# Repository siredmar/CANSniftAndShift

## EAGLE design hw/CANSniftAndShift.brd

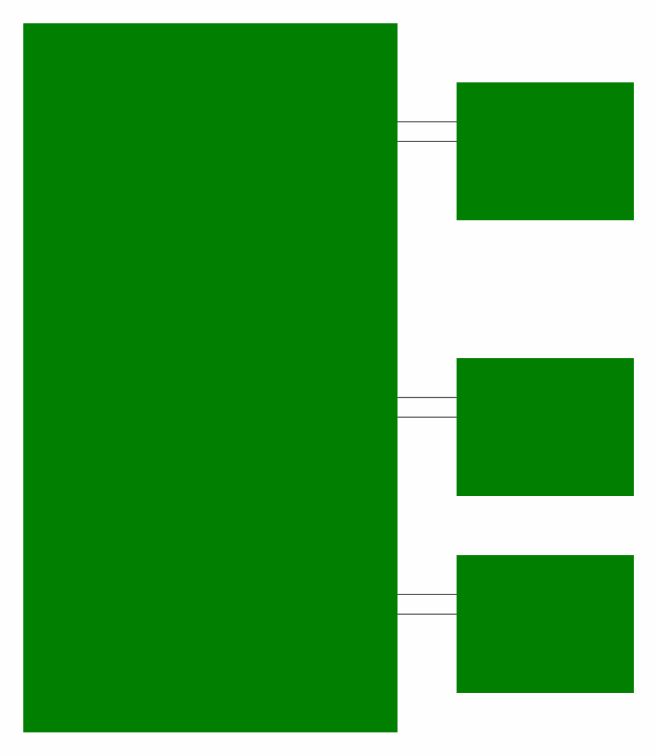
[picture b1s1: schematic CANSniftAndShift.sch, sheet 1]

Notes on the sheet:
CAN0
CAN1
CPU
FTDI
FTDI_RX
FTDI_TX
TXD
RXD
CAN0RX
CAN1RX
CAN0TX
CAN1TX
CANH
CANL

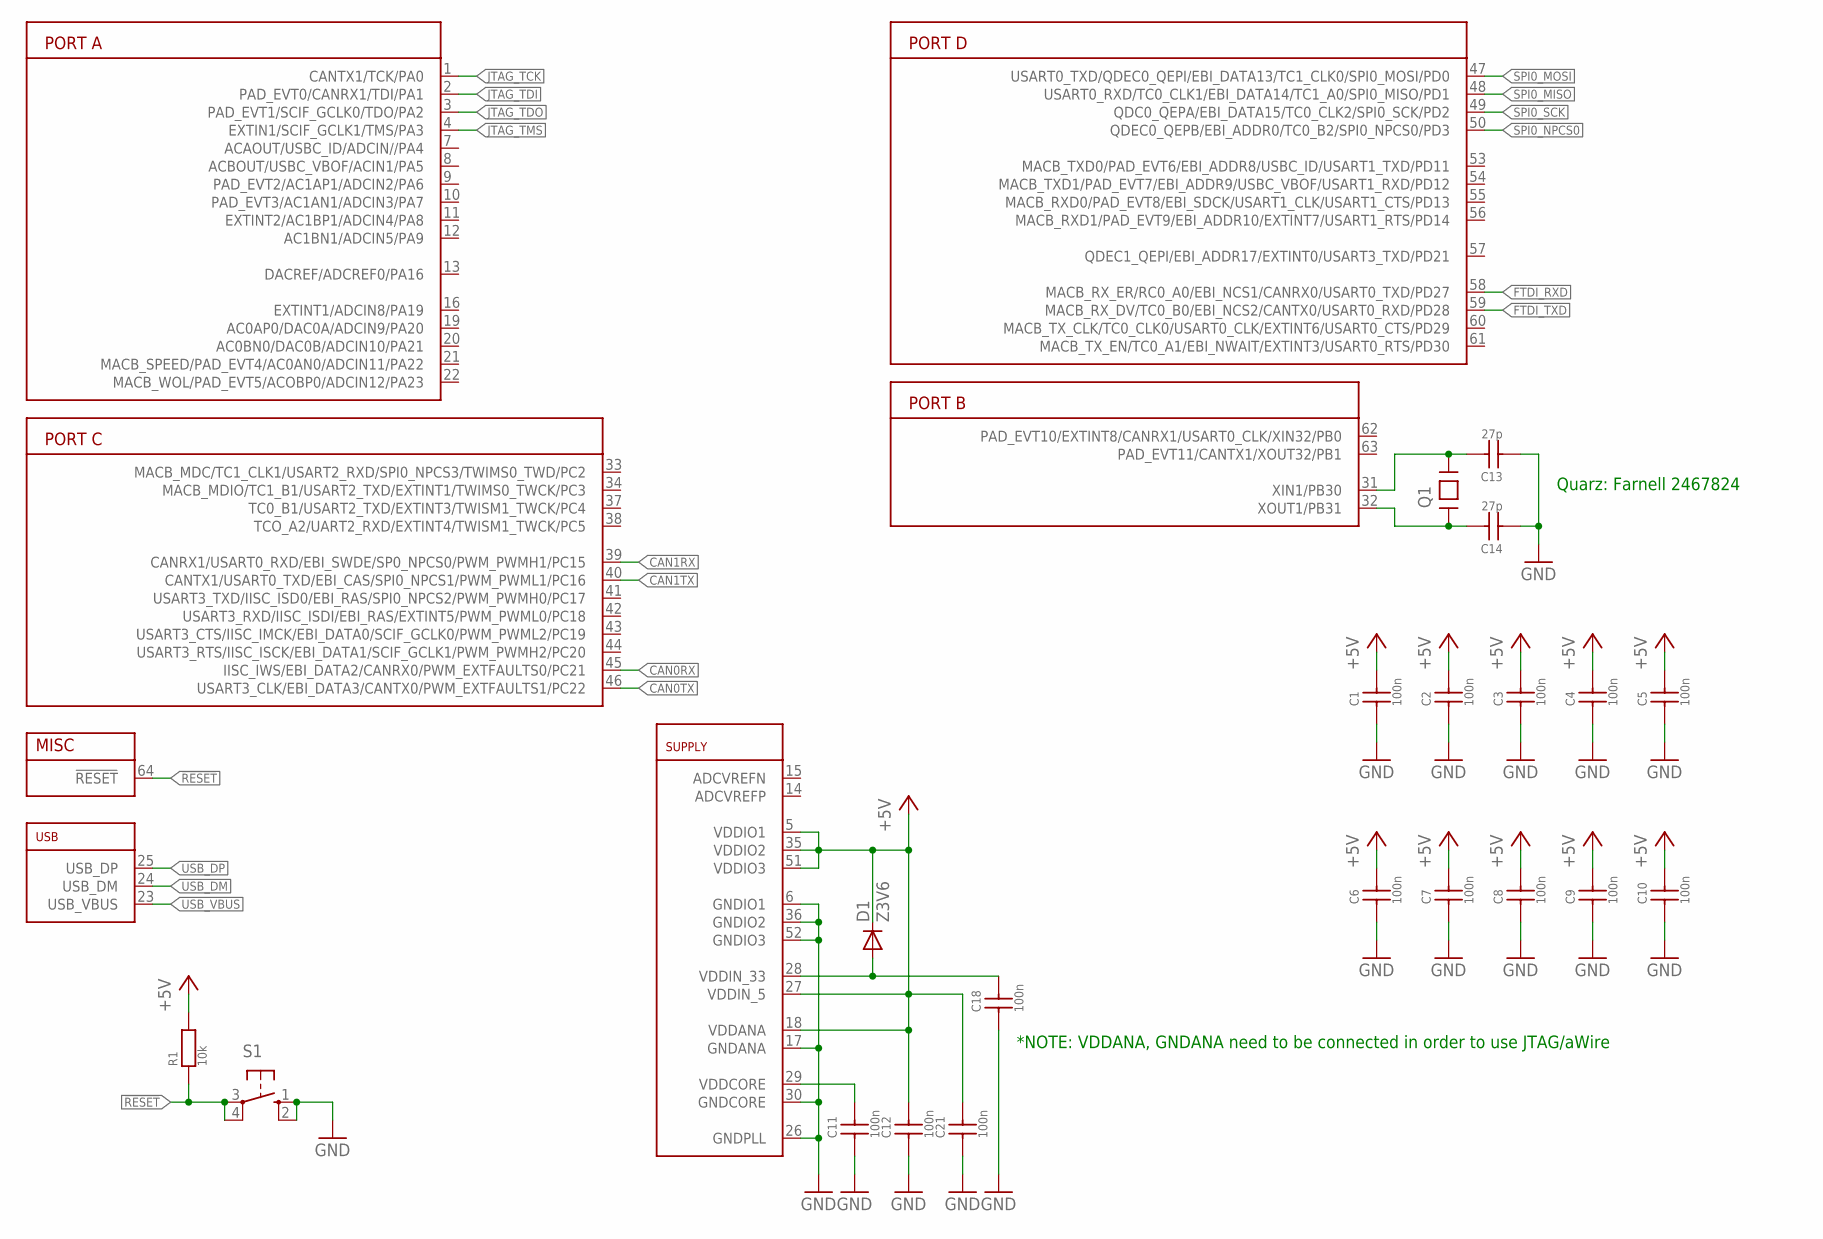
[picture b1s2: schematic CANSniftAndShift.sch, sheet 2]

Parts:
C1, C2, C3, C4, C5, C6, C7, C8, C9, C10, C11, C12, C18, C21: 100n; C0603
C13, C14: 27p; C0603
D1: Z3V6; DO214A
IC1: AT32UC3C264C0.5MM; TQFP64-0.5MM
Q1: 16MHz; CRYSTAL-ABRACON-ABM7-SMD
R1: 10k; R0603
S1: 10-XX; B3F-10XX

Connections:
!RESET: IC1.64 (!RESET), R1.1, S1.3, S1.4 (P1); also elsewhere on the board
+5V: C1.2, C2.2, C3.2, C4.2, C5.2, C6.2, C7.2, C8.2, C9.2, C10.2, C12.2, C21.2, D1.C, IC1.5 (VDDIO1), IC1.18 (VDDANA), IC1.27 (VDDIN_5), IC1.35 (VDDIO2), IC1.51 (VDDIO3), R1.2; also elsewhere on the board
CAN0RX: IC1.45 (IISC_IWS/EBI_DATA2/CANRX0/PWM_EXTFAULTS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); also elsewhere on the board
CAN0TX: IC1.46 (USART3_CLK/EBI_DATA3/CANTX0/PWM_EXTFAUL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); also elsewhere on the board
CAN1RX: IC1.39 (CANRX1/USART0_RXD/EBI_SWDE/SP0_NPCS0/PW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); also elsewhere on the board
CAN1TX: IC1.40 (CANTX1/USART0_TXD/EBI_CAS/SPI0_NPCS1/PW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); also elsewhere on the board
FTDI_RXD: IC1.58 (MACB_RX_ER/RC0_A0/EBI_NCS1/CANRX0/USART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); also elsewhere on the board
FTDI_TXD: IC1.59 (MACB_RX_DV/TC0_B0/EBI_NCS2/CANTX0/USART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); also elsewhere on the board
GND: C1.1, C2.1, C3.1, C4.1, C5.1, C6.1, C7.1, C8.1, C9.1, C10.1, C11.1, C12.1, C13.1, C14.1, C18.1, C21.1, IC1.6 (GNDIO1), IC1.17 (GNDANA), IC1.26 (GNDPLL), IC1.30 (GNDCORE), IC1.36 (GNDIO2), IC1.52 (GNDIO3), S1.1 (S), S1.2 (S1); also elsewhere on the board
JTAG_TCK: IC1.1 (CANTX1/TCK/PA0); also elsewhere on the board
JTAG_TDI: IC1.2 (PAD_EVT0/CANRX1/TDI/PA1); also elsewhere on the board
JTAG_TDO: IC1.3 (PAD_EVT1/SCIF_GCLK0/TDO/PA2); also elsewhere on the board
JTAG_TMS: IC1.4 (EXTIN1/SCIF_GCLK1/TMS/PA3); also elsewhere on the board
unnamed: C11.2, IC1.29 (VDDCORE)
unnamed: C13.2, IC1.31 (XIN1/PB30), Q1.P$2
unnamed: C14.2, IC1.32 (XOUT1/PB31), Q1.P$1
unnamed: C18.2, D1.A, IC1.28 (VDDIN_33)
SPI0_MISO: IC1.48 (USART0_RXD/TC0_CLK1/EBI_DATA14/TC1_A0/S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)
SPI0_MOSI: IC1.47 (USART0_TXD/QDEC0_QEPI/EBI_DATA13/TC1_CL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)
SPI0_NPCS0: IC1.50 (QDEC0_QEPB/EBI_ADDR0/TC0_B2/SPI0_NPCS0/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)
SPI0_SCK: IC1.49 (QDC0_QEPA/EBI_DATA15/TC0_CLK2/SPI0_SCK/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)
USB_DM: IC1.24 (USB_DM); also elsewhere on the board
USB_DP: IC1.25 (USB_DP); also elsewhere on the board
USB_VBUS: IC1.23 (USB_VBUS); also elsewhere on the board

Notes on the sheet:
Quarz: Farnell 2467824
*NOTE: VDDANA, GNDANA need to be connected in order to use JTAG/aWire

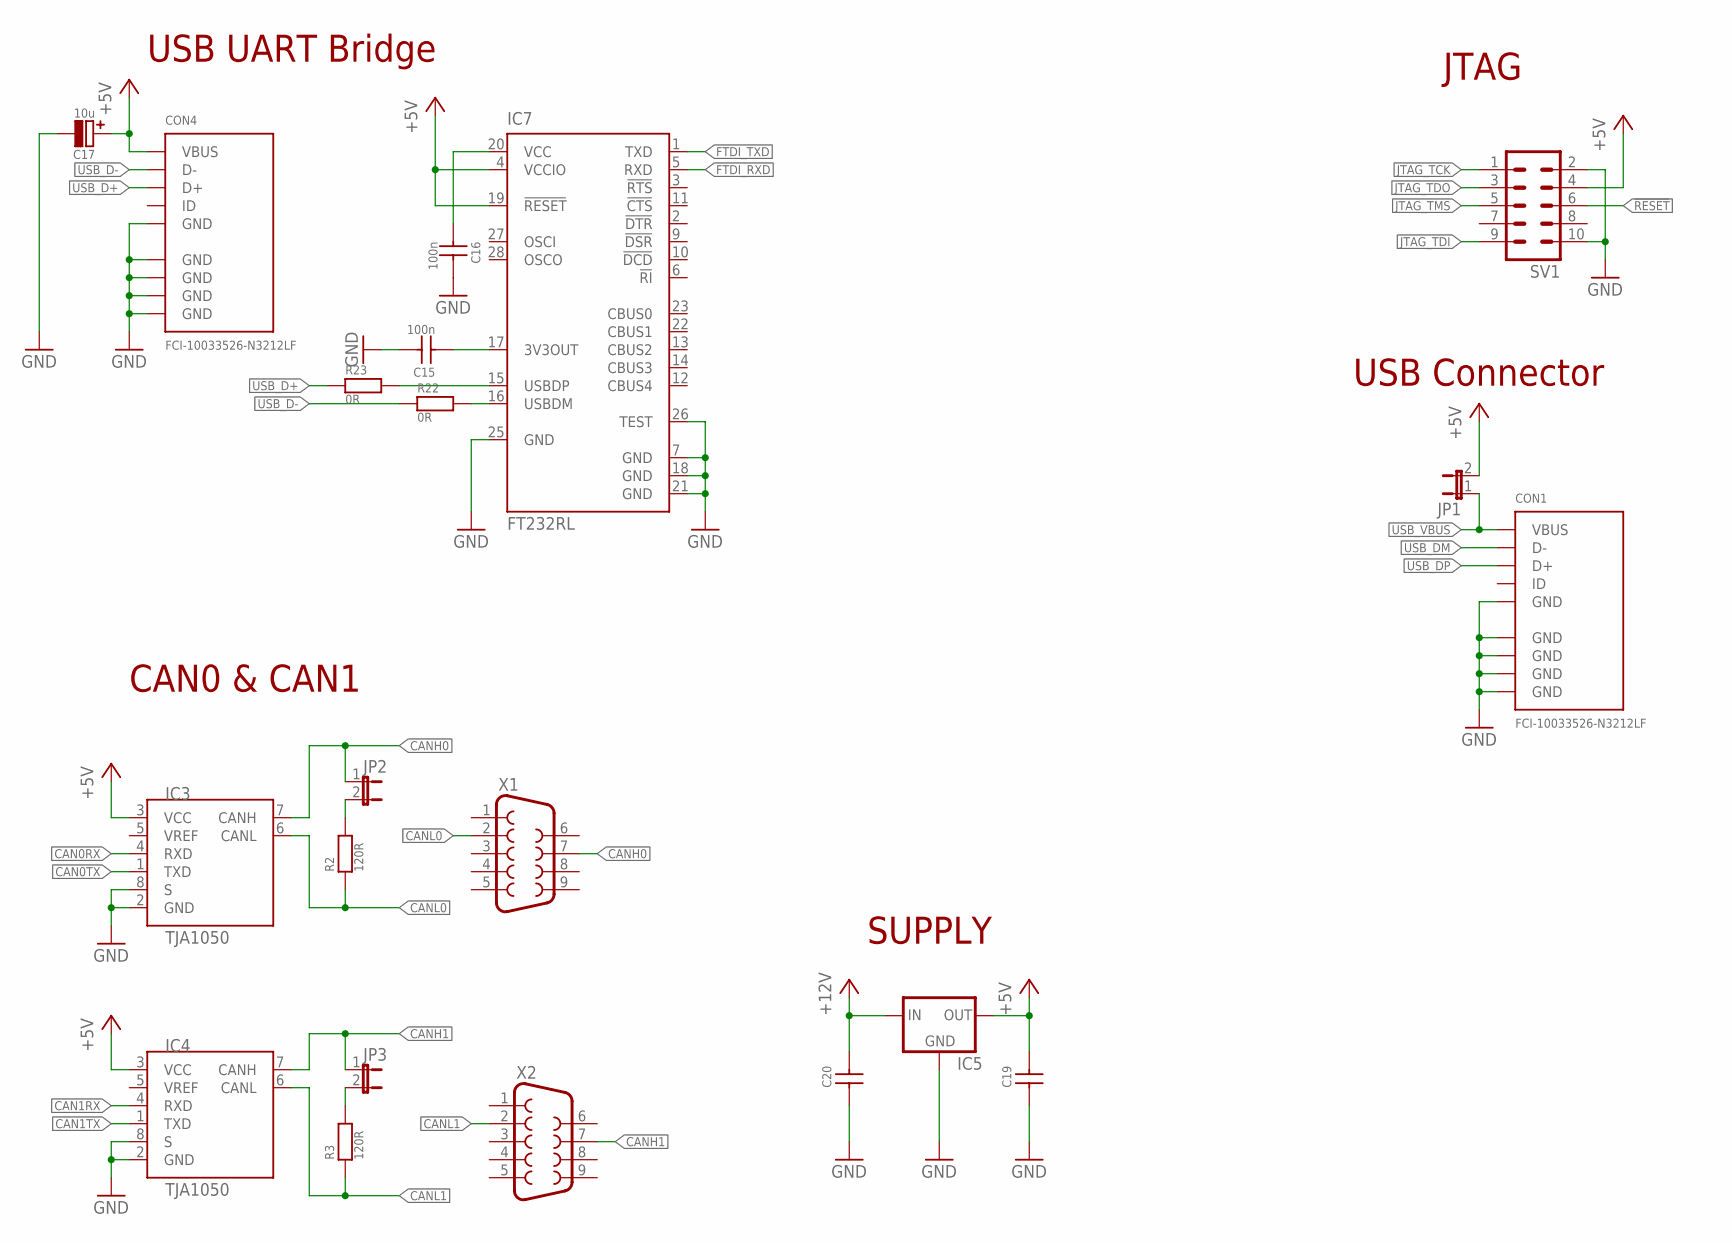
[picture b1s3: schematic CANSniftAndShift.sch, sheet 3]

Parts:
C15, C16: 100n; C0402
C17: 10u; C_POL_4X4MM
C19, C20: C_SMD0603; C0603
CON1, CON4: FCI-10033526-N3212LF
IC3, IC4: TJA1050; SO8
IC5: 78XXL
IC7: FT232RL; SSOP28
JP1, JP2, JP3: JUMPER2; JUMPER2_THROUGHHOLE
R2, R3: 120R; R0603
R22, R23: 0R; R0402
SV1: ML10
X1, X2: F09HP

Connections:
!RESET: SV1.6; also elsewhere on the board
+5V: C17.+, C19.2, CON4.1 (VBUS), IC3.3 (VCC), IC4.3 (VCC), IC5.OUT, IC7.4 (VCCIO), IC7.19 (!RESET), JP1.2, SV1.4; also elsewhere on the board
+12V: C20.2, IC5.IN
CAN0RX: IC3.4 (RXD); also elsewhere on the board
CAN0TX: IC3.1 (TXD); also elsewhere on the board
CAN1RX: IC4.4 (RXD); also elsewhere on the board
CAN1TX: IC4.1 (TXD); also elsewhere on the board
CANH0: IC3.7 (CANH), JP2.1, X1.7
CANH1: IC4.7 (CANH), JP3.1, X2.7
CANL0: IC3.6 (CANL), R2.1, X1.2
CANL1: IC4.6 (CANL), R3.1, X2.2
FTDI_3V3OUT: C15.1, IC7.17 (3V3OUT)
FTDI_RXD: IC7.5 (RXD); also elsewhere on the board
FTDI_TXD: IC7.1 (TXD); also elsewhere on the board
GND: C15.2, C16.2, C17.-, C19.1, C20.1, CON1.5 (GND), CON1.GND@1 (GND), CON1.GND@2 (GND), CON1.GND@3 (GND), CON1.GND@4 (GND), CON4.5 (GND), CON4.GND@1 (GND), CON4.GND@2 (GND), CON4.GND@3 (GND), CON4.GND@4 (GND), IC3.2 (GND), IC3.8 (S), IC4.2 (GND), IC4.8 (S), IC5.GND, IC7.7 (GND), IC7.18 (GND), IC7.21 (GND), IC7.25 (GND), IC7.26 (TEST), SV1.2, SV1.10; also elsewhere on the board
JTAG_TCK: SV1.1; also elsewhere on the board
JTAG_TDI: SV1.9; also elsewhere on the board
JTAG_TDO: SV1.3; also elsewhere on the board
JTAG_TMS: SV1.5; also elsewhere on the board
unnamed: IC7.15 (USBDP), R23.2
unnamed: IC7.16 (USBDM), R22.2
unnamed: JP2.2, R2.2
unnamed: JP3.2, R3.2
unnamed: C16.1, IC7.20 (VCC)
USB_D+: CON4.3 (D+), R23.1
USB_D-: CON4.2 (D-), R22.1
USB_DM: CON1.2 (D-); also elsewhere on the board
USB_DP: CON1.3 (D+); also elsewhere on the board
USB_VBUS: CON1.1 (VBUS), JP1.1; also elsewhere on the board

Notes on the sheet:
USB UART Bridge
JTAG
USB Connector
CAN0 & CAN1
SUPPLY

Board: 2 copper layers, 42 parts (0 on the bottom side), 33 nets, no tracks yet.

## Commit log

2015-05-06 added requirements
2015-05-06 add first version of lbr
2015-05-06 modified schematics
2015-05-09 updated lbr and schematics
2015-05-11 modified schematic
2015-05-12 modified lbr
2015-05-12 first version of schematic
2015-05-12 added new lbr
2015-05-13 updated sch
2015-05-13 test
2015-05-13 added datasheets
2015-05-13 added embedded sw frame, started to work on port driver
2015-05-15 first version of Port driver
2015-05-15 added README.txt containing installation steps for AVR32 toolchain
2015-05-15 Port driver mod
2015-05-15 bugfix Port driver
2015-05-20 updated lbr AT32 package (wrong footprint used), added Dio driver, modified Port driver
2015-05-20 Port and Dio driver now working
2015-05-22 removed duplicated code
2015-06-05 sw modified
2015-06-05 added initial ASF configuration to project
2015-06-07 added many ASF drivers, PLL, UART, Delay now working, USB to come
